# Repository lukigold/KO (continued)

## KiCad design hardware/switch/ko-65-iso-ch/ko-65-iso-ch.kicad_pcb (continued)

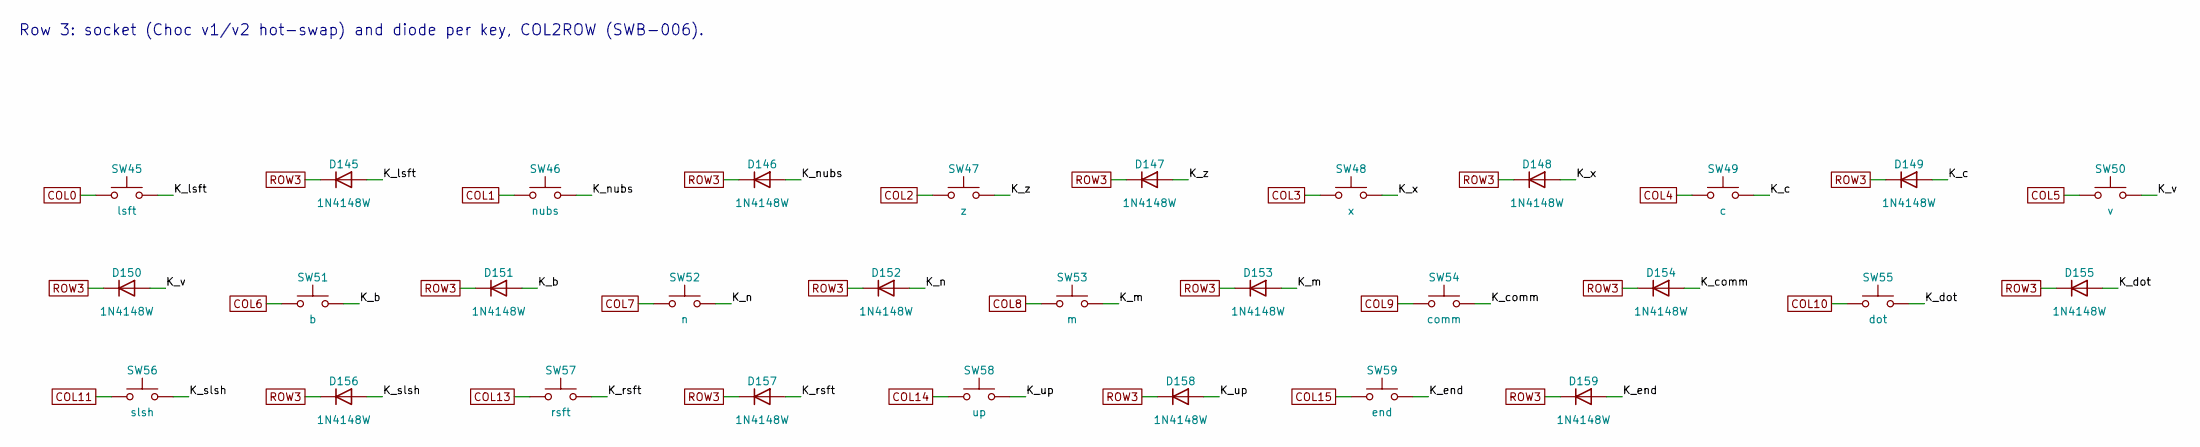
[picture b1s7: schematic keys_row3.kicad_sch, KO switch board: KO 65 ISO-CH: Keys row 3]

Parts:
D145, D146, D147, D148, D149, D150, D151, D152, D153, D154, D155, D156, D157, D158, D159: 1N4148W; D_SOD-123; MPN 1N4148W; LCSC C81598
SW45: lsft; Key_Choc_V1V2_Hotswap_CPG1350; MPN Kailh CPG135001S30
SW46: nubs; Key_Choc_V1V2_Hotswap_CPG1350; MPN Kailh CPG135001S30
SW47: z; Key_Choc_V1V2_Hotswap_CPG1350; MPN Kailh CPG135001S30
SW48: x; Key_Choc_V1V2_Hotswap_CPG1350; MPN Kailh CPG135001S30
SW49: c; Key_Choc_V1V2_Hotswap_CPG1350; MPN Kailh CPG135001S30
SW50: v; Key_Choc_V1V2_Hotswap_CPG1350; MPN Kailh CPG135001S30
SW51: b; Key_Choc_V1V2_Hotswap_CPG1350; MPN Kailh CPG135001S30
SW52: n; Key_Choc_V1V2_Hotswap_CPG1350; MPN Kailh CPG135001S30
SW53: m; Key_Choc_V1V2_Hotswap_CPG1350; MPN Kailh CPG135001S30
SW54: comm; Key_Choc_V1V2_Hotswap_CPG1350; MPN Kailh CPG135001S30
SW55: dot; Key_Choc_V1V2_Hotswap_CPG1350; MPN Kailh CPG135001S30
SW56: slsh; Key_Choc_V1V2_Hotswap_CPG1350; MPN Kailh CPG135001S30
SW57: rsft; Key_Choc_V1V2_Hotswap_CPG1350; MPN Kailh CPG135001S30
SW58: up; Key_Choc_V1V2_Hotswap_CPG1350; MPN Kailh CPG135001S30
SW59: end; Key_Choc_V1V2_Hotswap_CPG1350; MPN Kailh CPG135001S30

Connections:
/Keys row 3/K_b: D151.2 (A), SW51.2
/Keys row 3/K_c: D149.2 (A), SW49.2
/Keys row 3/K_comm: D154.2 (A), SW54.2
/Keys row 3/K_dot: D155.2 (A), SW55.2
/Keys row 3/K_end: D159.2 (A), SW59.2
/Keys row 3/K_lsft: D145.2 (A), SW45.2
/Keys row 3/K_m: D153.2 (A), SW53.2
/Keys row 3/K_n: D152.2 (A), SW52.2
/Keys row 3/K_nubs: D146.2 (A), SW46.2
/Keys row 3/K_rsft: D157.2 (A), SW57.2
/Keys row 3/K_slsh: D156.2 (A), SW56.2
/Keys row 3/K_up: D158.2 (A), SW58.2
/Keys row 3/K_v: D150.2 (A), SW50.2
/Keys row 3/K_x: D148.2 (A), SW48.2
/Keys row 3/K_z: D147.2 (A), SW47.2
COL0: SW45.1; also elsewhere on the board
COL1: SW46.1; also elsewhere on the board
COL2: SW47.1; also elsewhere on the board
COL3: SW48.1; also elsewhere on the board
COL4: SW49.1; also elsewhere on the board
COL5: SW50.1; also elsewhere on the board
COL6: SW51.1; also elsewhere on the board
COL7: SW52.1; also elsewhere on the board
COL8: SW53.1; also elsewhere on the board
COL9: SW54.1; also elsewhere on the board
COL10: SW55.1; also elsewhere on the board
COL11: SW56.1; also elsewhere on the board
COL13: SW57.1; also elsewhere on the board
COL14: SW58.1; also elsewhere on the board
COL15: SW59.1; also elsewhere on the board
ROW3: D145.1 (K), D146.1 (K), D147.1 (K), D148.1 (K), D149.1 (K), D150.1 (K), D151.1 (K), D152.1 (K), D153.1 (K), D154.1 (K), D155.1 (K), D156.1 (K), D157.1 (K), D158.1 (K), D159.1 (K); also elsewhere on the board

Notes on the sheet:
Row 3: socket (Choc v1/v2 hot-swap) and diode per key, COL2ROW (SWB-006).

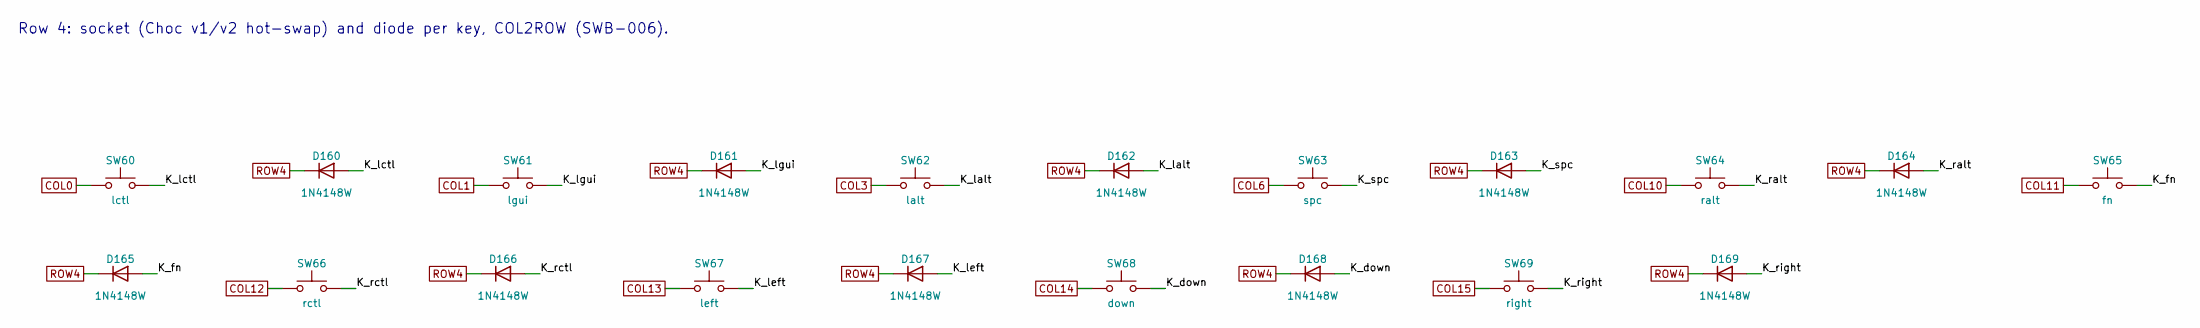
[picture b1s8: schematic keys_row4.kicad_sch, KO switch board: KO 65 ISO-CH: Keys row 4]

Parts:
D160, D161, D162, D163, D164, D165, D166, D167, D168, D169: 1N4148W; D_SOD-123; MPN 1N4148W; LCSC C81598
SW60: lctl; Key_Choc_V1V2_Hotswap_CPG1350; MPN Kailh CPG135001S30
SW61: lgui; Key_Choc_V1V2_Hotswap_CPG1350; MPN Kailh CPG135001S30
SW62: lalt; Key_Choc_V1V2_Hotswap_CPG1350; MPN Kailh CPG135001S30
SW63: spc; Key_Choc_V1V2_Hotswap_CPG1350; MPN Kailh CPG135001S30
SW64: ralt; Key_Choc_V1V2_Hotswap_CPG1350; MPN Kailh CPG135001S30
SW65: fn; Key_Choc_V1V2_Hotswap_CPG1350; MPN Kailh CPG135001S30
SW66: rctl; Key_Choc_V1V2_Hotswap_CPG1350; MPN Kailh CPG135001S30
SW67: left; Key_Choc_V1V2_Hotswap_CPG1350; MPN Kailh CPG135001S30
SW68: down; Key_Choc_V1V2_Hotswap_CPG1350; MPN Kailh CPG135001S30
SW69: right; Key_Choc_V1V2_Hotswap_CPG1350; MPN Kailh CPG135001S30

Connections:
/Keys row 4/K_down: D168.2 (A), SW68.2
/Keys row 4/K_fn: D165.2 (A), SW65.2
/Keys row 4/K_lalt: D162.2 (A), SW62.2
/Keys row 4/K_lctl: D160.2 (A), SW60.2
/Keys row 4/K_left: D167.2 (A), SW67.2
/Keys row 4/K_lgui: D161.2 (A), SW61.2
/Keys row 4/K_ralt: D164.2 (A), SW64.2
/Keys row 4/K_rctl: D166.2 (A), SW66.2
/Keys row 4/K_right: D169.2 (A), SW69.2
/Keys row 4/K_spc: D163.2 (A), SW63.2
COL0: SW60.1; also elsewhere on the board
COL1: SW61.1; also elsewhere on the board
COL3: SW62.1; also elsewhere on the board
COL6: SW63.1; also elsewhere on the board
COL10: SW64.1; also elsewhere on the board
COL11: SW65.1; also elsewhere on the board
COL12: SW66.1; also elsewhere on the board
COL13: SW67.1; also elsewhere on the board
COL14: SW68.1; also elsewhere on the board
COL15: SW69.1; also elsewhere on the board
ROW4: D160.1 (K), D161.1 (K), D162.1 (K), D163.1 (K), D164.1 (K), D165.1 (K), D166.1 (K), D167.1 (K), D168.1 (K), D169.1 (K); also elsewhere on the board

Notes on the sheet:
Row 4: socket (Choc v1/v2 hot-swap) and diode per key, COL2ROW (SWB-006).

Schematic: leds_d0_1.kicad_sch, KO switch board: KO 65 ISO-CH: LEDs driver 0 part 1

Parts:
D301, D302, D303, D304, D305, D306, D307, D308, D309, D310, D311, D312, D313, D316, D317, D318, D319, D320, D321, D322, D323, D324, D325, D326, D327, D328, D331, D332, D333, D334, D335, D336, D337, D338, D339, D340, D341, D342, D343, D345, D346, D347, D348, D349, D350, D351, D352, D353, D354, D355, D356, D357: E6CC1205RGBC3UDA; LED_E6CC1205RGBC3UDA_ReverseMount; MPN E6CC1205RGBC3UDA; LCSC C2802677

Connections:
D0_CS1: D301.4 (B), D316.4 (B), D331.4 (B), D345.4 (B); also elsewhere on the board
D0_CS2: D301.3 (G), D316.3 (G), D331.3 (G), D345.3 (G); also elsewhere on the board
D0_CS3: D301.1 (R), D316.1 (R), D331.1 (R), D345.1 (R); also elsewhere on the board
D0_CS4: D302.4 (B), D317.4 (B), D332.4 (B), D346.4 (B); also elsewhere on the board
D0_CS5: D302.3 (G), D317.3 (G), D332.3 (G), D346.3 (G); also elsewhere on the board
D0_CS6: D302.1 (R), D317.1 (R), D332.1 (R), D346.1 (R); also elsewhere on the board
D0_CS7: D303.4 (B), D318.4 (B), D333.4 (B), D347.4 (B); also elsewhere on the board
D0_CS8: D303.3 (G), D318.3 (G), D333.3 (G), D347.3 (G); also elsewhere on the board
D0_CS9: D303.1 (R), D318.1 (R), D333.1 (R), D347.1 (R); also elsewhere on the board
D0_CS10: D304.4 (B), D319.4 (B), D334.4 (B), D348.4 (B); also elsewhere on the board
D0_CS11: D304.3 (G), D319.3 (G), D334.3 (G), D348.3 (G); also elsewhere on the board
D0_CS12: D304.1 (R), D319.1 (R), D334.1 (R), D348.1 (R); also elsewhere on the board
D0_CS13: D305.4 (B), D320.4 (B), D335.4 (B), D349.4 (B); also elsewhere on the board
D0_CS14: D305.3 (G), D320.3 (G), D335.3 (G), D349.3 (G); also elsewhere on the board
D0_CS15: D305.1 (R), D320.1 (R), D335.1 (R), D349.1 (R); also elsewhere on the board
D0_CS16: D306.4 (B), D321.4 (B), D336.4 (B), D350.4 (B); also elsewhere on the board
D0_CS17: D306.3 (G), D321.3 (G), D336.3 (G), D350.3 (G); also elsewhere on the board
D0_CS18: D306.1 (R), D321.1 (R), D336.1 (R), D350.1 (R); also elsewhere on the board
D0_CS19: D307.4 (B), D322.4 (B), D337.4 (B), D351.4 (B); also elsewhere on the board
D0_CS20: D307.3 (G), D322.3 (G), D337.3 (G), D351.3 (G); also elsewhere on the board
D0_CS21: D307.1 (R), D322.1 (R), D337.1 (R), D351.1 (R); also elsewhere on the board
D0_CS22: D308.4 (B), D323.4 (B), D338.4 (B), D352.4 (B); also elsewhere on the board
D0_CS23: D308.3 (G), D323.3 (G), D338.3 (G), D352.3 (G); also elsewhere on the board
D0_CS24: D308.1 (R), D323.1 (R), D338.1 (R), D352.1 (R); also elsewhere on the board
D0_CS25: D309.4 (B), D324.4 (B), D339.4 (B), D353.4 (B); also elsewhere on the board
D0_CS26: D309.3 (G), D324.3 (G), D339.3 (G), D353.3 (G); also elsewhere on the board
D0_CS27: D309.1 (R), D324.1 (R), D339.1 (R), D353.1 (R); also elsewhere on the board
D0_CS28: D310.4 (B), D325.4 (B), D340.4 (B), D354.4 (B); also elsewhere on the board
D0_CS29: D310.3 (G), D325.3 (G), D340.3 (G), D354.3 (G); also elsewhere on the board
D0_CS30: D310.1 (R), D325.1 (R), D340.1 (R), D354.1 (R); also elsewhere on the board
D0_CS31: D311.4 (B), D326.4 (B), D341.4 (B), D355.4 (B); also elsewhere on the board
D0_CS32: D311.3 (G), D326.3 (G), D341.3 (G), D355.3 (G); also elsewhere on the board
D0_CS33: D311.1 (R), D326.1 (R), D341.1 (R), D355.1 (R); also elsewhere on the board
D0_CS34: D312.4 (B), D327.4 (B), D342.4 (B), D356.4 (B); also elsewhere on the board
D0_CS35: D312.3 (G), D327.3 (G), D342.3 (G), D356.3 (G); also elsewhere on the board
D0_CS36: D312.1 (R), D327.1 (R), D342.1 (R), D356.1 (R); also elsewhere on the board
D0_CS37: D313.4 (B), D328.4 (B), D343.4 (B), D357.4 (B); also elsewhere on the board
D0_CS38: D313.3 (G), D328.3 (G), D343.3 (G), D357.3 (G); also elsewhere on the board
D0_CS39: D313.1 (R), D328.1 (R), D343.1 (R), D357.1 (R); also elsewhere on the board
D0_SW1: D301.2 (A), D302.2 (A), D303.2 (A), D304.2 (A), D305.2 (A), D306.2 (A), D307.2 (A), D308.2 (A), D309.2 (A), D310.2 (A), D311.2 (A), D312.2 (A), D313.2 (A); also elsewhere on the board
D0_SW2: D316.2 (A), D317.2 (A), D318.2 (A), D319.2 (A), D320.2 (A), D321.2 (A), D322.2 (A), D323.2 (A), D324.2 (A), D325.2 (A), D326.2 (A), D327.2 (A), D328.2 (A); also elsewhere on the board
D0_SW3: D331.2 (A), D332.2 (A), D333.2 (A), D334.2 (A), D335.2 (A), D336.2 (A), D337.2 (A), D338.2 (A), D339.2 (A), D340.2 (A), D341.2 (A), D342.2 (A), D343.2 (A); also elsewhere on the board
D0_SW4: D345.2 (A), D346.2 (A), D347.2 (A), D348.2 (A), D349.2 (A), D350.2 (A), D351.2 (A), D352.2 (A), D353.2 (A), D354.2 (A), D355.2 (A), D356.2 (A), D357.2 (A); also elsewhere on the board

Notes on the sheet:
Driver 0: anodes on SW lines 1, 2, 3, 4, cathodes on CS (R = CS3s+3, G = 3s+2, B = 3s+1 for slot s). Key LEDs reverse mount, underglow facing down.

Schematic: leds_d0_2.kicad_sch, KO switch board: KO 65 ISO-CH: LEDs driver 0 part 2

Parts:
D314, D315, D329, D330, D344, D358, D359, D360, D361, D362, D363, D364, D365, D366, D367, D368, D369: E6CC1205RGBC3UDA; LED_E6CC1205RGBC3UDA_ReverseMount; MPN E6CC1205RGBC3UDA; LCSC C2802677
D501, D502, D503, D504, D505, D506, D507, D508, D509, D510, D511, D512, D513, D514, D515, D516, D517, D518: E6CC1205RGBC3UDA; LED_E6CC1205RGBC3UDA_Underglow; MPN E6CC1205RGBC3UDA; LCSC C2802677

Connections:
D0_CS1: D360.4 (B), D501.4 (B), D516.4 (B), D517.4 (B), D518.4 (B); also elsewhere on the board
D0_CS2: D360.3 (G), D501.3 (G), D516.3 (G), D517.3 (G), D518.3 (G); also elsewhere on the board
D0_CS3: D360.1 (R), D501.1 (R), D516.1 (R), D517.1 (R), D518.1 (R); also elsewhere on the board
D0_CS4: D361.4 (B); also elsewhere on the board
D0_CS5: D361.3 (G); also elsewhere on the board
D0_CS6: D361.1 (R); also elsewhere on the board
D0_CS7: D362.4 (B), D502.4 (B), D515.4 (B); also elsewhere on the board
D0_CS8: D362.3 (G), D502.3 (G), D515.3 (G); also elsewhere on the board
D0_CS9: D362.1 (R), D502.1 (R), D515.1 (R); also elsewhere on the board
D0_CS13: D503.4 (B), D514.4 (B); also elsewhere on the board
D0_CS14: D503.3 (G), D514.3 (G); also elsewhere on the board
D0_CS15: D503.1 (R), D514.1 (R); also elsewhere on the board
D0_CS16: D363.4 (B), D513.4 (B); also elsewhere on the board
D0_CS17: D363.3 (G), D513.3 (G); also elsewhere on the board
D0_CS18: D363.1 (R), D513.1 (R); also elsewhere on the board
D0_CS19: D504.4 (B); also elsewhere on the board
D0_CS20: D504.3 (G); also elsewhere on the board
D0_CS21: D504.1 (R); also elsewhere on the board
D0_CS25: D364.4 (B), D505.4 (B), D512.4 (B); also elsewhere on the board
D0_CS26: D364.3 (G), D505.3 (G), D512.3 (G); also elsewhere on the board
D0_CS27: D364.1 (R), D505.1 (R), D512.1 (R); also elsewhere on the board
D0_CS28: D365.4 (B), D506.4 (B), D511.4 (B); also elsewhere on the board
D0_CS29: D365.3 (G), D506.3 (G), D511.3 (G); also elsewhere on the board
D0_CS30: D365.1 (R), D506.1 (R), D511.1 (R); also elsewhere on the board
D0_CS31: D366.4 (B), D507.4 (B), D508.4 (B), D509.4 (B), D510.4 (B); also elsewhere on the board
D0_CS32: D366.3 (G), D507.3 (G), D508.3 (G), D509.3 (G), D510.3 (G); also elsewhere on the board
D0_CS33: D366.1 (R), D507.1 (R), D508.1 (R), D509.1 (R), D510.1 (R); also elsewhere on the board
D0_CS34: D314.4 (B), D329.4 (B), D358.4 (B), D367.4 (B), D369.4 (B); also elsewhere on the board
D0_CS35: D314.3 (G), D329.3 (G), D358.3 (G), D367.3 (G), D369.3 (G); also elsewhere on the board
D0_CS36: D314.1 (R), D329.1 (R), D358.1 (R), D367.1 (R), D369.1 (R); also elsewhere on the board
D0_CS37: D315.4 (B), D330.4 (B), D344.4 (B), D359.4 (B), D368.4 (B); also elsewhere on the board
D0_CS38: D315.3 (G), D330.3 (G), D344.3 (G), D359.3 (G), D368.3 (G); also elsewhere on the board
D0_CS39: D315.1 (R), D330.1 (R), D344.1 (R), D359.1 (R), D368.1 (R); also elsewhere on the board
D0_SW5: D360.2 (A), D361.2 (A), D362.2 (A), D363.2 (A), D364.2 (A), D365.2 (A), D366.2 (A), D367.2 (A), D368.2 (A); also elsewhere on the board
D0_SW6: D314.2 (A), D315.2 (A), D501.2 (A), D502.2 (A), D503.2 (A), D504.2 (A), D505.2 (A), D506.2 (A), D507.2 (A), D513.2 (A); also elsewhere on the board
D0_SW7: D329.2 (A), D330.2 (A), D508.2 (A), D511.2 (A), D512.2 (A), D514.2 (A), D515.2 (A), D516.2 (A); also elsewhere on the board
D0_SW8: D344.2 (A), D358.2 (A), D509.2 (A), D517.2 (A); also elsewhere on the board
D0_SW9: D359.2 (A), D369.2 (A), D510.2 (A), D518.2 (A); also elsewhere on the board

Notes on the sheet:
Driver 0: anodes on SW lines 5, 6, 7, 8, 9, cathodes on CS (R = CS3s+3, G = 3s+2, B = 3s+1 for slot s). Key LEDs reverse mount, underglow facing down.

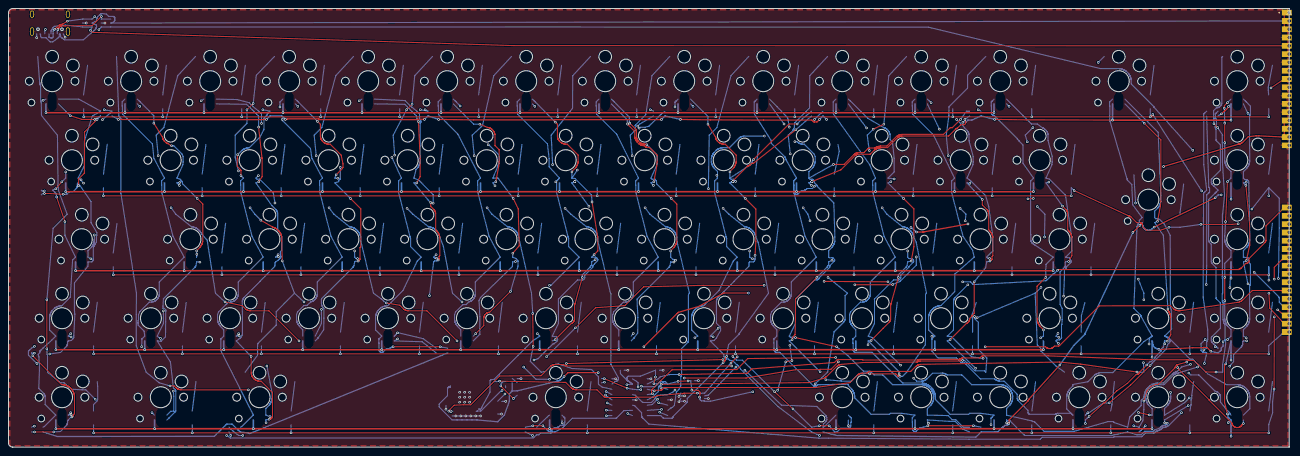
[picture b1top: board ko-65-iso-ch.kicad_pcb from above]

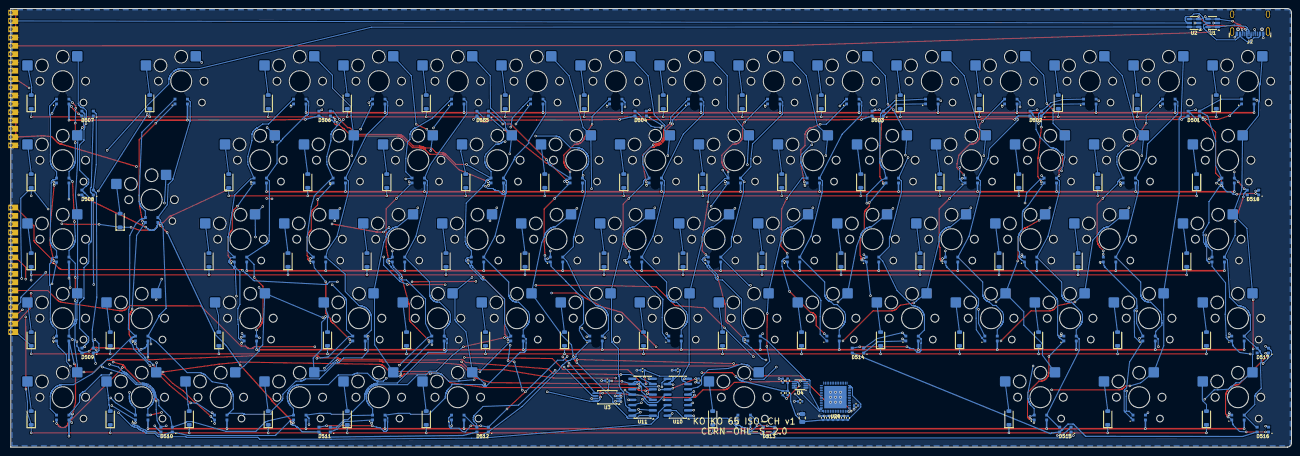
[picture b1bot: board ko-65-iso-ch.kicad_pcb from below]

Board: 4 copper layers, 308.8 x 105.8 mm, 251 parts (181 on the bottom side), 158 nets.

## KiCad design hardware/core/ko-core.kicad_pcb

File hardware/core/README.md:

# KO core board (KiCad project)

- **Contract:** [docs/contracts/core-board.md](../../docs/contracts/core-board.md)
- **Design note (parts, power tree, pin map, schematic decisions):** [docs/design/core-board-rev-a.md](../../docs/design/core-board-rev-a.md)
- **Status:** rev A as a 19 × 80 mm strip beside the keys (D-41, D-43, D-45, D-55, D-56): schematic verified, PCB placed by script, fully routed (4 layers, DRC clean, D-56), JLCPCB files in `fab/`. Only USB-C port A and the battery connector are connectors; switch, NTC, SWD, haptic and underglow wires solder to pads on the bottom.

## The schematic is generated

`tools/gen_schematic.py` is the source of truth: every part, value, footprint, LCSC number and net is defined
there. It writes the KiCad files below. **Do not edit the schematic in KiCad**; your changes would be overwritten.
Edit the Python, then regenerate and check:

```bash
python3 hardware/core/tools/gen_schematic.py
```

```bash
python3 hardware/core/tools/check_schematic.py out/
```

The check fails on any ERC error and on any difference between KiCad's netlist and the intended nets. It also
writes `ko-core-schematic.pdf` and `ko-core-bom.csv` to the output folder.

| File | Content |
|---|---|
| `ko-core.kicad_sch` | Root sheet with the six block sheets |
| `power.kicad_sch` | Battery and charger: BQ25628E, LiPo and NTC connectors, MAX17048 |
| `power_rails.kicad_sch` | Power switch, 3.0 V LDO, 5 V boost, 5 V mux, LED rail switch |
| `mcu_radio.kicad_sch` | BMD-340 (nRF52840), 32.768 kHz crystal, I²C pull-ups |
| `usb.kicad_sch` | USB-C port A, port B inputs, TPS2121 VBUS mux, TS3USB221A data switch, CC resistors, ESD |
| `switchboard_conn.kicad_sch` | 33 castellated contacts to the switch board (pinout fixed by the contract) |
| `service.kicad_sch` | SWD header, test points, haptic connector (DNP), underglow port |
| `lib/ko.kicad_sym`, `sym-lib-table` | Project symbols drawn from datasheets (generated) |
| `bom/parts_query.json`, `bom/parts.csv` | Part queries and resolved LCSC numbers (`hardware/tools/jlc_lookup.py`) |
| `ko-core.kicad_pcb`, `ko-core.kicad_pro` | 4-layer, 1.0 mm, 19 × 80 mm strip, generated by `tools/gen_pcb.py` (placement, net classes, planes, antenna keep-out) |
| `lib/ko.pretty`, `fp-lib-table` | Custom footprints, generated by `tools/gen_footprints.py` from the manufacturers' drawings |
| `route/ko-core-maze.json` | Routed tracks and vias found by the grid maze router (source of truth for them) |
| `fab/` | Rev A manufacturing files, written by `tools/fab_outputs.py` |
| `tools/` | `gen_schematic.py` (design data), `check_schematic.py` (verification), `gen_footprints.py`, `gen_pcb.py` (placement), `route_pcb.py` (hand-routed power and buses, GND fan-out, maze routing, stitching, zone fill); run the PCB scripts with KiCad's Python: `/usr/bin/python3` |

The generator library lives in [`hardware/tools/kisch`](../tools/kisch) and will be reused for the switch board,
the dongle and the modules.

## The PCB is generated too

```bash
/usr/bin/python3 hardware/core/tools/gen_pcb.py
```

```bash
/usr/bin/python3 hardware/core/tools/route_pcb.py
```

`gen_pcb.py` places every part from the schematic netlist. `route_pcb.py` rebuilds the copper: the power paths
drawn in code, a GND via for every SMD GND pad, the stored maze-router tracks
(`route/ko-core-maze.json`), stitching vias and the pours. `route_pcb.py --maze` routes again whatever is open
(set `MAZE_CACHE=/some/file.json` to keep the slow negotiation step between runs).
`route_pcb.py --repair` closes connections that are still open by moving only the stored routes in their way;
`route_pcb.py --polish` removes dead router leftovers. The negotiation runs in one worker process per CPU core
(`MAZE_WORKERS=N` to choose). The A* search is C (`hardware/tools/astar.c`, compiled by `maze.py` on first use;
needs a C compiler, e.g. `apt install build-essential`, else it falls back to the slow Python search with the same
paths), and the maps of the kept routes are updated in place. On 8 threads `--maze` with `MAZE_ITERS=40
MAZE_ATTEMPTS=32` takes about 4-5 minutes and `--repair` about 2 minutes (before: about 80 minutes in all). WSL2 may show fewer threads than the CPU has: set
`processors=<n>` under `[wsl2]` in `%UserProfile%\.wslconfig` and run `wsl --shutdown`.

### Running the routing on your own computer

The scripts need Linux with KiCad 9 (its `pcbnew` Python module and `kicad-cli`), numpy and git. On Windows use
WSL2 with Ubuntu 24.04; it sees all CPU threads by default.

1. Windows PowerShell as administrator, then restart Windows:

```powershell
wsl --install -d Ubuntu-24.04
```

2. In the Ubuntu terminal: KiCad 9 from the KiCad PPA, numpy and git:

```bash
sudo add-apt-repository -y ppa:kicad/kicad-9.0-releases && sudo apt update && sudo apt install -y kicad python3-numpy git
```

3. Clone this repository (branch `p1/core-strip`) inside the Linux file system (not under `/mnt/c`, which is slow):

```bash
cd ~ && git clone -b p1/core-strip https://github.com/lukigold/ko.git && cd ko
```

4. Check the toolchain: the schematic check must end with `RESULT: PASS`.

```bash
/usr/bin/python3 hardware/core/tools/gen_schematic.py && /usr/bin/python3 hardware/core/tools/check_schematic.py
```

5. Route. `MAZE_WORKERS` is the number of parallel worker processes (default: all CPU threads); the negotiation
   and the legalisation attempts both run in parallel. `MAZE_CACHE` keeps the negotiation result, so a second run
   with the same placement starts at the legalisation.

```bash
MAZE_CACHE=/tmp/ko-neg.json MAZE_ATTEMPTS=16 /usr/bin/python3 -u hardware/core/tools/route_pcb.py --maze
```

```bash
/usr/bin/python3 -u hardware/core/tools/route_pcb.py --repair && /usr/bin/python3 -u hardware/core/tools/route_pcb.py --polish
```

```bash
kicad-cli pcb drc --schematic-parity --severity-all hardware/core/ko-core.kicad_pcb
```

Repeat `--repair` while it still closes connections. `fab_outputs.py` then writes the ordering files once DRC is
clean.

### Where the strip stands (D-43, D-44, D-45)

- Schematic, contracts, placement and the hand-drawn copper are done and DRC clean before routing (ERC and
  netlist check pass). The strip is 19 × 80 mm now (D-45, D-55, D-56): on 16 mm the router stopped at about 100 of 120
  connections with any placement.
- Latest run (2026-11-26, 19 mm strip, D-56): `MAZE_SEED=11 MAZE_ALL=1 MAZE_ITERS=40 MAZE_ATTEMPTS=32`, then
  `--repair` and `--polish`: **all connections routed, DRC 0 violations, 0 warnings, 0 unconnected, 0 parity issues.**
  Seeds 5 and 37 left 2-3 open. On 18 mm (D-55) the best was 2 open (ROW4, USB_DN), on 17 mm 2 open (ROW2,
  ROW3) after pin changes D-46 to D-54.
- Next: owner review (1:1 print fit check, JLCPCB placement preview), then order.
- `--maze` without `MAZE_MERGE` now ignores the stored routes (it replaces them); delete
  `route/ko-core-maze.json` before routing a changed placement from scratch.

## Manufacturing files

```bash
/usr/bin/python3 hardware/core/tools/fab_outputs.py
```

Writes `fab/`: Gerbers and drills (zip), JLCPCB BOM and CPL, a 1:1 PDF for the fit check and three renders. It
refuses to run unless DRC is clean. The rev A files are committed; see the design note, §9 "Ordering at JLCPCB",
for what to check before ordering.

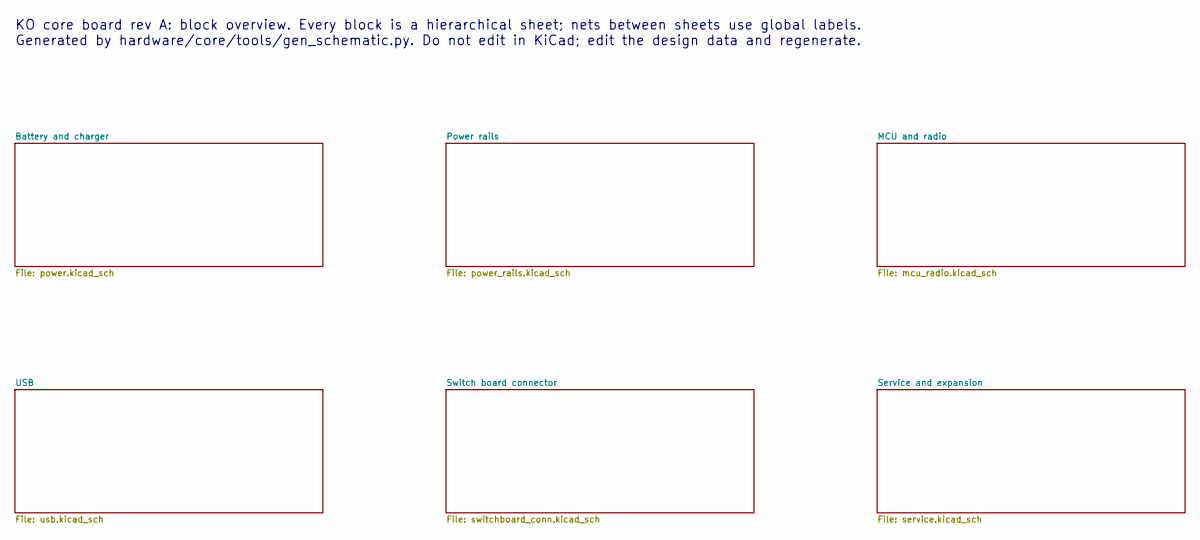
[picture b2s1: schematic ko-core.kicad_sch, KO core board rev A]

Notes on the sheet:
KO core board rev A: block overview. Every block is a hierarchical sheet; nets between sheets use global labels. Generated by hardware/core/tools/gen_schematic.py. Do not edit in KiCad; edit the design data and regenerate.

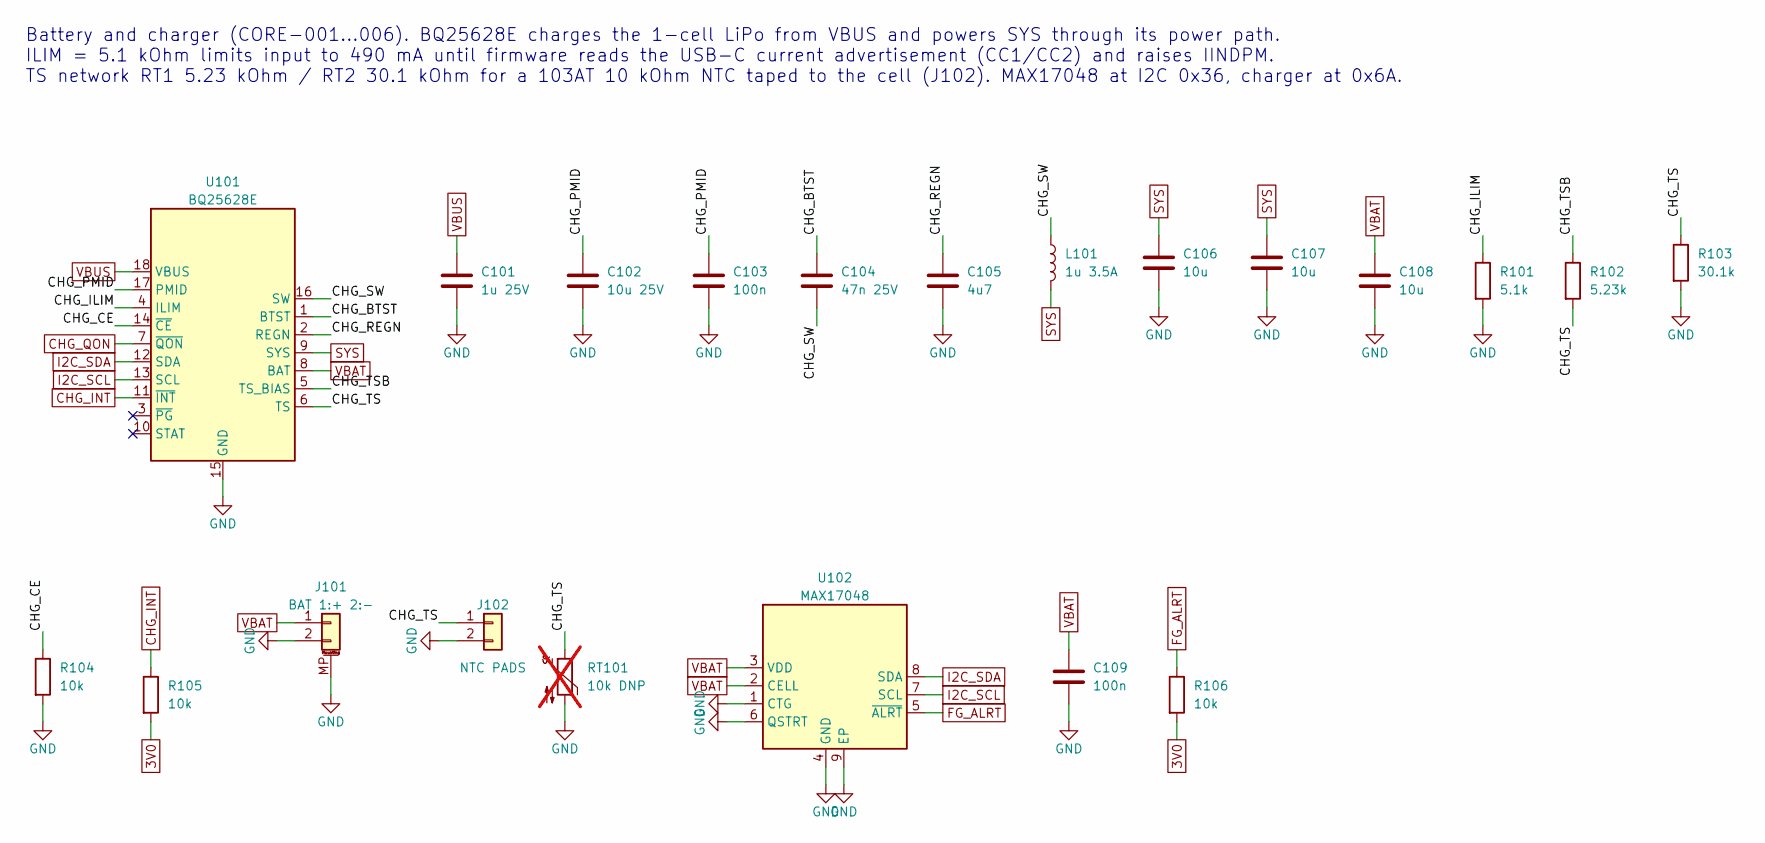
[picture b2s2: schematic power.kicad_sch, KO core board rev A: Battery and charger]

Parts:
C101: 1u 25V; C_0402_1005Metric; MPN CL05A105KA5NQNC; LCSC C52923
C102: 10u 25V; C_0805_2012Metric; MPN CL21A106KAYNNNE; LCSC C15850
C103, C109: 100n; C_0402_1005Metric; MPN CL05B104KO5NNNC; LCSC C1525
C104: 47n 25V; C_0402_1005Metric; MPN CC0402JRX7R9BB473; LCSC C576715
C105: 4u7; C_0603_1608Metric; MPN CL10A475KO8NNNC; LCSC C19666
C106, C107, C108: 10u; C_0603_1608Metric; MPN CL10A106KP8NNNC; LCSC C19702
J101: BAT 1:+ 2:-; JST_PH_S2B-PH-SM4-TB_1x02-1MP_P2.00mm_Horizontal; MPN XY-S2B-PH-SM4-TB; LCSC C54582899
J102: NTC PADS; WirePads_NTC
L101: 1u 3.5A; L_1008_2520Metric; MPN WPN252012E1R0MT; LCSC C370610
R101: 5.1k; R_0402_1005Metric; MPN 0402WGF5101TCE; LCSC C25905
R102: 5.23k; R_0402_1005Metric; MPN RMCF0402FT5K23; LCSC C2479336
R103: 30.1k; R_0402_1005Metric; MPN 0402WGF3012TCE; LCSC C29402
R104, R105, R106: 10k; R_0402_1005Metric; MPN 0402WGF1002TCE; LCSC C25744
RT101: 10k DNP; R_0402_1005Metric; MPN NCP15XH103F03RC; not fitted
U101: BQ25628E; Texas_RYK_WQFN-HR-18; MPN BQ25628ERYKR; LCSC C18221178
U102: MAX17048; TDFN-8-1EP_2x2mm_P0.5mm_EP0.8x1.2mm; MPN MAX17048G+T10; LCSC C2682616

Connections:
3V0: R105.2, R106.2; also elsewhere on the board
/Battery and charger/CHG_BTST: C104.1, U101.1 (BTST)
/Battery and charger/CHG_CE: R104.1, U101.14 (~CE)
/Battery and charger/CHG_ILIM: R101.1, U101.4 (ILIM)
/Battery and charger/CHG_PMID: C102.1, C103.1, U101.17 (PMID)
/Battery and charger/CHG_REGN: C105.1, U101.2 (REGN)
/Battery and charger/CHG_SW: C104.2, L101.1, U101.16 (SW)
/Battery and charger/CHG_TS: J102.1, R102.2, R103.1, RT101.1, U101.6 (TS)
/Battery and charger/CHG_TSB: R102.1, U101.5 (TS_BIAS)
CHG_INT: R105.1, U101.11 (~INT); also elsewhere on the board
CHG_QON: U101.7 (~QON); also elsewhere on the board
FG_ALRT: R106.1, U102.5 (~ALRT); also elsewhere on the board
GND: C101.2, C102.2, C103.2, C105.2, C106.2, C107.2, C108.2, C109.2, J101.2, J101.MP (MountPin), J102.2, R101.2, R103.2, R104.2, RT101.2, U101.15 (GND), U102.1 (CTG), U102.4 (GND), U102.6 (QSTRT), U102.9 (EP); also elsewhere on the board
I2C_SCL: U101.13 (SCL), U102.7 (SCL); also elsewhere on the board
I2C_SDA: U101.12 (SDA), U102.8 (SDA); also elsewhere on the board
SYS: C106.1, C107.1, L101.2, U101.9 (SYS); also elsewhere on the board
VBAT: C108.1, C109.1, J101.1, U101.8 (BAT), U102.2 (CELL), U102.3 (VDD); also elsewhere on the board
VBUS: C101.1, U101.18 (VBUS); also elsewhere on the board

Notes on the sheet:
Battery and charger (CORE-001...006). BQ25628E charges the 1-cell LiPo from VBUS and powers SYS through its power path. ILIM = 5.1 kOhm limits input to 490 mA until firmware reads the USB-C current advertisement (CC1/CC2) and raises IINDPM. TS network RT1 5.23 kOhm / RT2 30.1 kOhm for a 103AT 10 kO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

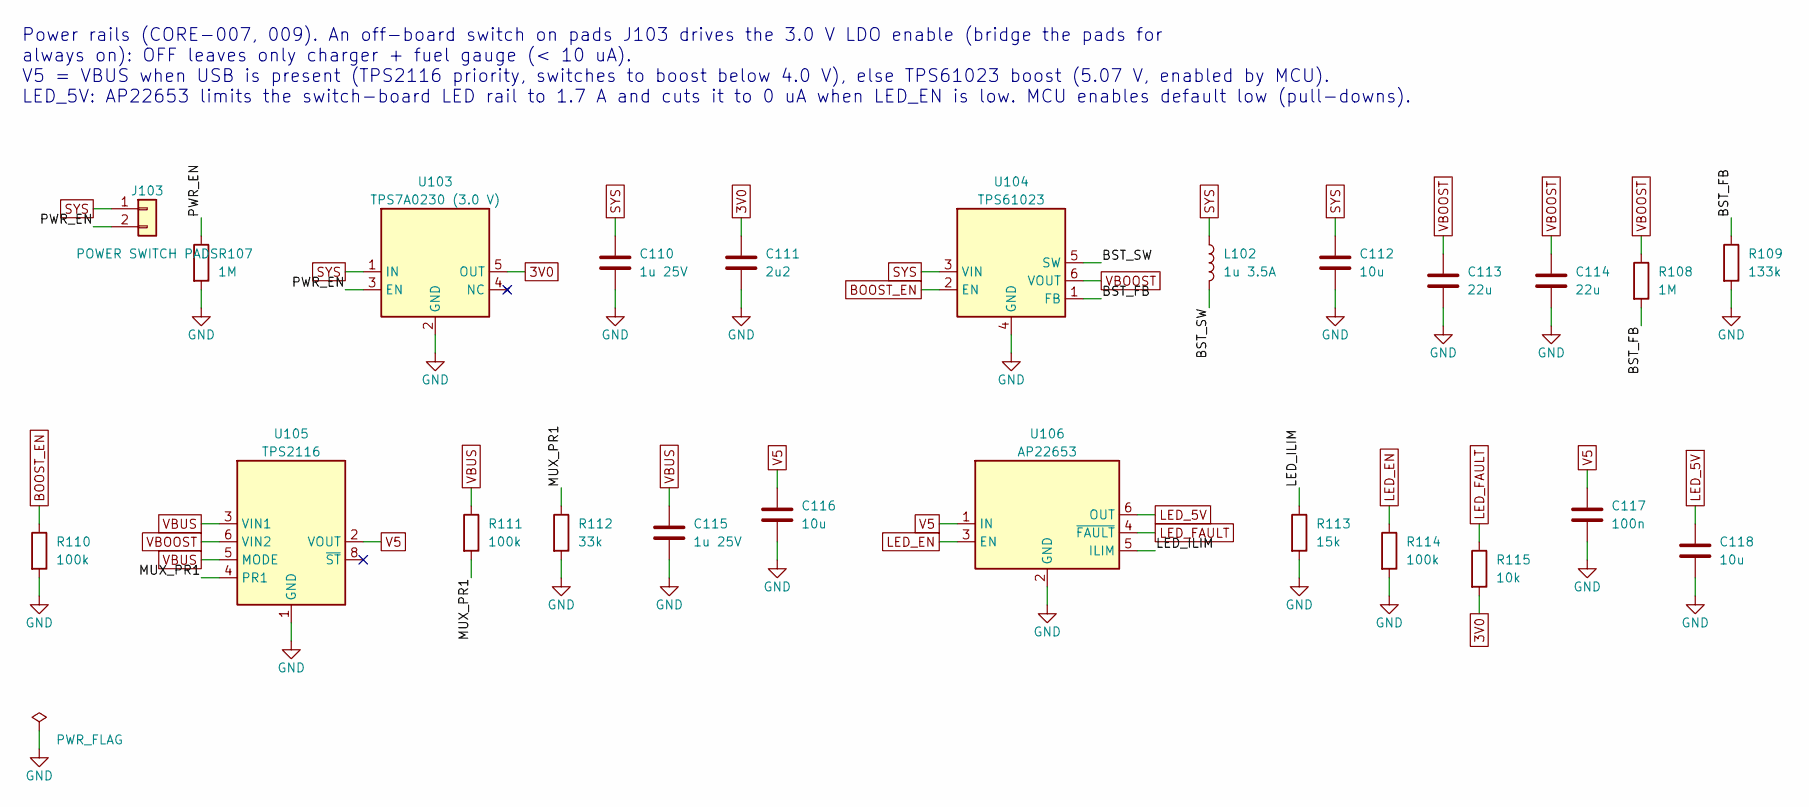
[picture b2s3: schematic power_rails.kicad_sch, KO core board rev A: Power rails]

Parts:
C110, C115: 1u 25V; C_0402_1005Metric; MPN CL05A105KA5NQNC; LCSC C52923
C111: 2u2; C_0402_1005Metric; MPN GRM155Z71A225KE44D; LCSC C2999759
C112, C116, C118: 10u; C_0603_1608Metric; MPN CL10A106KP8NNNC; LCSC C19702
C113, C114: 22u; C_0805_2012Metric; MPN CL21A226MAQNNNE; LCSC C45783
C117: 100n; C_0402_1005Metric; MPN CL05B104KO5NNNC; LCSC C1525
J103: POWER SWITCH PADS; WirePads_Switch
L102: 1u 3.5A; L_1008_2520Metric; MPN WPN252012E1R0MT; LCSC C370610
R107, R108: 1M; R_0402_1005Metric; MPN 0402WGF1004TCE; LCSC C26083
R109: 133k; R_0402_1005Metric; MPN 0402WGF1333TCE; LCSC C25753
R110, R111, R114: 100k; R_0402_1005Metric; MPN 0402WGF1003TCE; LCSC C25741
R112: 33k; R_0402_1005Metric; MPN 0402WGF3302TCE; LCSC C25779
R113: 15k; R_0402_1005Metric; MPN 0402WGF1502TCE; LCSC C25756
R115: 10k; R_0402_1005Metric; MPN 0402WGF1002TCE; LCSC C25744
U103: TPS7A0230 (3.0 V); SOT-23-5; MPN TPS7A0230PDBVR; LCSC C3747031
U104: TPS61023; SOT-563; MPN TPS61023DRLR; LCSC C919459
U105: TPS2116; SOT-583-8; MPN TPS2116DRLR; LCSC C3235557
U106: AP22653; SOT-23-6; MPN AP22653W6-7; LCSC C2158037

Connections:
3V0: C111.1, R115.2, U103.5 (OUT); also elsewhere on the board
/Power rails/BST_FB: R108.2, R109.1, U104.1 (FB)
/Power rails/BST_SW: L102.2, U104.5 (SW)
/Power rails/LED_ILIM: R113.1, U106.5 (ILIM)
/Power rails/MUX_PR1: R111.2, R112.1, U105.4 (PR1)
/Power rails/PWR_EN: J103.2, R107.1, U103.3 (EN)
BOOST_EN: R110.1, U104.2 (EN); also elsewhere on the board
GND: C110.2, C111.2, C112.2, C113.2, C114.2, C115.2, C116.2, C117.2, C118.2, R107.2, R109.2, R110.2, R112.2, R113.2, R114.2, U103.2 (GND), U104.4 (GND), U105.1 (GND), U106.2 (GND); also elsewhere on the board
LED_5V: C118.1, U106.6 (OUT); also elsewhere on the board
LED_EN: R114.1, U106.3 (EN); also elsewhere on the board
LED_FAULT: R115.1, U106.4 (~FAULT); also elsewhere on the board
SYS: C110.1, C112.1, J103.1, L102.1, U103.1 (IN), U104.3 (VIN); also elsewhere on the board
V5: C116.1, C117.1, U105.2 (VOUT), U105.7 (VOUT), U106.1 (IN); also elsewhere on the board
VBOOST: C113.1, C114.1, R108.1, U104.6 (VOUT), U105.6 (VIN2); also elsewhere on the board
VBUS: C115.1, R111.1, U105.3 (VIN1), U105.5 (MODE); also elsewhere on the board

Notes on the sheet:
Power rails (CORE-007, 009). An off-board switch on pads J103 drives the 3.0 V LDO enable (bridge the pads for always on): OFF leaves only charger + fuel gauge (< 10 uA). V5 = VBUS when USB is present (TPS2116 priority, switches to boost below 4.0 V), else TPS61023 boost (5.07 V, enabled by MCU). L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
